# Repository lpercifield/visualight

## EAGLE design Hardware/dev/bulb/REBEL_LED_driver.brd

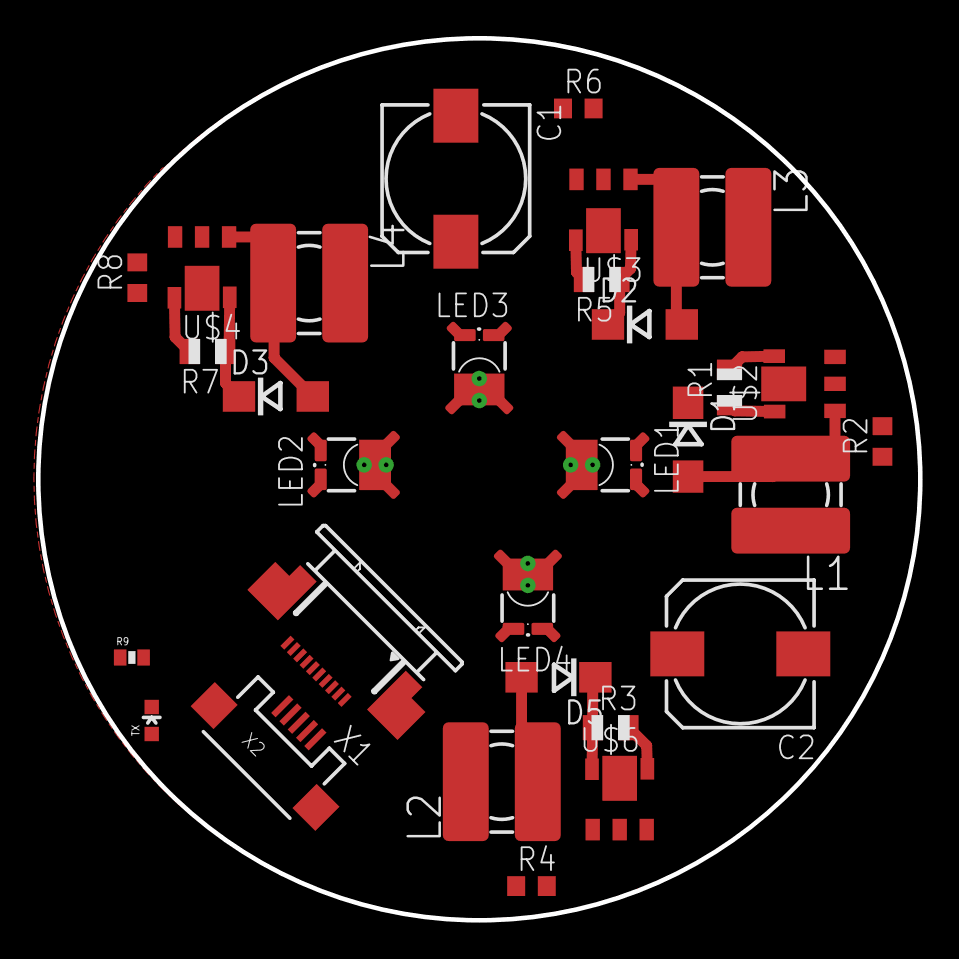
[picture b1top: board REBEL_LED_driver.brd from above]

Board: 2 copper layers, 49.0 x 49.0 mm, 30 parts (0 on the bottom side), 28 nets.

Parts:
C1, C2: 150uF; 175TMP-0810
D1, D2, D3, D5: SCHOTTKY; DO214AC
L1, L2, L3, L4: 47uH; TDK6045
LED1, LED2, LED3, LED4: LUXEON_REBEL
R1, R3, R5, R7: 0.14; R0805
R2, R4, R6, R8: 10K; R0603
R9: 330; 0402-RES
TX: Green; LED-0603
U$2, U$3, U$4, U$6: ZLED7000-LEDDRIVER; SOT89-5
X1: 52745-1090
X2: USB-MICROB

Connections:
D5: R6.1, X1.3
D9: R2.1, X1.5
D10: R8.1, X1.4
D13: R4.1, X1.2
D+IN: X1.7, X2.D+
D-IN: X1.8, X2.D-
GND: C1.-, C2.-, U$2.2, U$3.2, U$4.2, U$6.2, X1.9, X2.GND
unnamed: R2.2, U$2.3
unnamed: R9.2, TX.C
unnamed: LED1.A, LED1.A@1, R1.2, U$2.4
unnamed: L1.1, LED1.C, LED1.C@1
unnamed: D1.A, L1.2, U$2.1
unnamed: LED4.A, LED4.A@1, R3.2, U$6.4
unnamed: D5.A, L2.2, U$6.1
unnamed: R4.2, U$6.3
unnamed: LED3.A, LED3.A@1, R5.2, U$3.4
unnamed: D2.A, L3.2, U$3.1
unnamed: R6.2, U$3.3
unnamed: LED2.A, LED2.A@1, R7.2, U$4.4
unnamed: D3.A, L4.2, U$4.1
unnamed: R8.2, U$4.3
unnamed: L4.1, LED2.C, LED2.C@1
unnamed: L2.1, LED4.C, LED4.C@1
unnamed: L3.1, LED3.C, LED3.C@1
TH: LED1.TH, LED1.TH@1, LED1.TH@2, LED1.TH@3, LED1.TH@4, LED2.TH, LED2.TH@1, LED2.TH@2, LED2.TH@3, LED2.TH@4, LED3.TH, LED3.TH@1, LED3.TH@2, LED3.TH@3, LED3.TH@4, LED4.TH, LED4.TH@1, LED4.TH@2, LED4.TH@3, LED4.TH@4
TXLED: R9.1, X1.6
UVCC: TX.A, X1.1, X2.VBUS
VCC: C1.+, C2.+, D1.C, D2.C, D3.C, D5.C, R1.1, R3.1, R5.1, R7.1, U$2.5, U$3.5, U$4.5, U$6.5, X1.10

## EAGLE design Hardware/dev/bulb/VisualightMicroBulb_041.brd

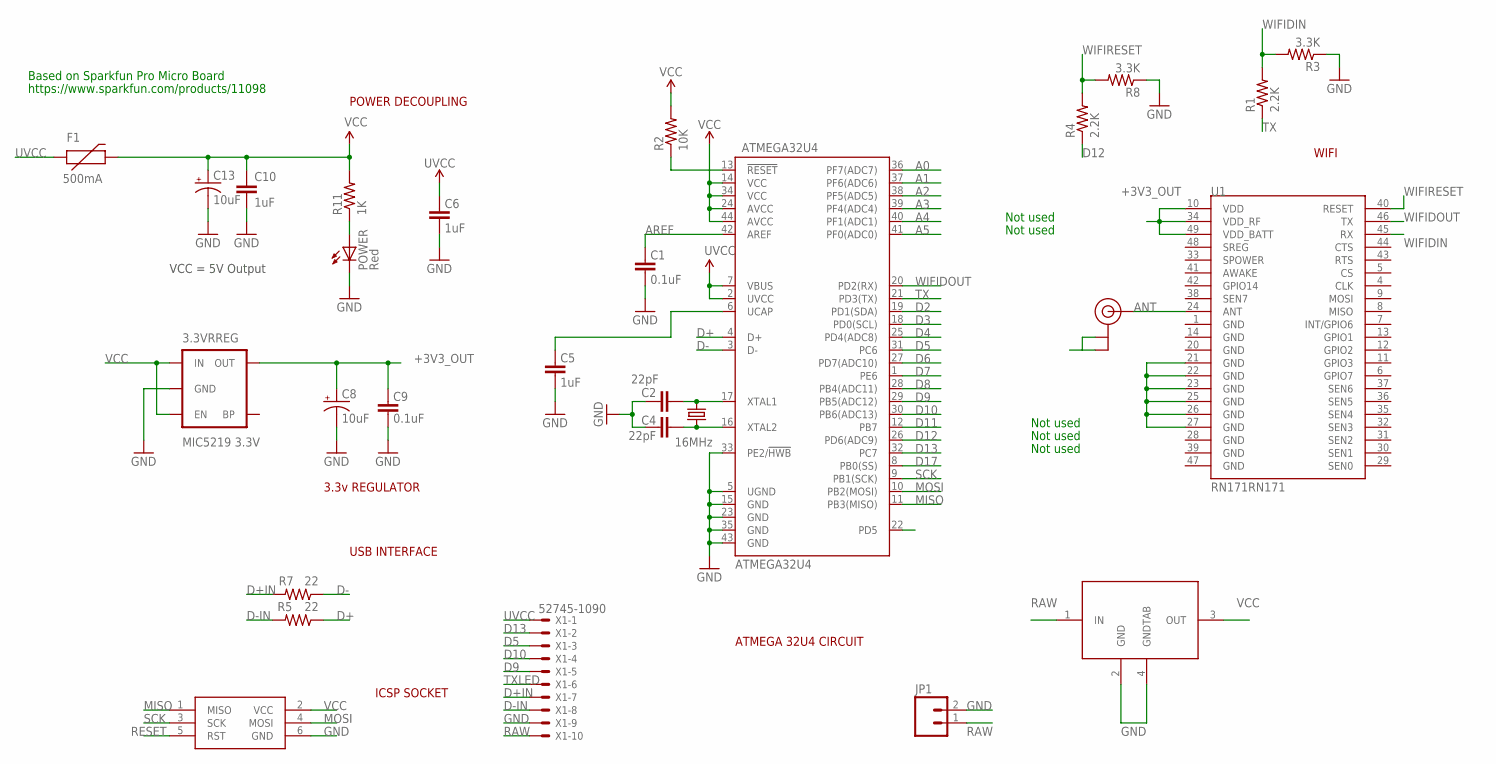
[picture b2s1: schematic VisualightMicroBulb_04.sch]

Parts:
3.3VRREG: MIC5219 3.3V; SOT23-5
ATMEGA32U4: ATMEGA32U4; SPARKFUN-DIGITALIC_TQFP44
C1, C9: 0.1uF; 0402-CAP
C2, C4: 22pF; 0402-CAP
C5, C6, C10: 1uF; 0402-CAP
C8, C13: 10uF; EIA3216
F1: 500mA; PTC-1206
ISP1: AVRISP-6; AVRISP
JP1: M02PTH; 1X02
POWER: Red; LED-0603
R1, R4: 2.2K; 0402-RES
R2: 10K; 0402-RES
R3, R8: 3.3K; 0402-RES
R5, R7: 22; 0402-RES
R11: 1K; 0402-RES
U1: RN171RN171; RN171
U$1: U.FL
U$2: MIC5239; SOT223
X1: 52745-1090
Y1: 16MHz; CRYSTAL-SMD-5X3

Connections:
+3V3_OUT: 3.3VRREG.5 (OUT), C8.A (+), C9.2, U1.10 (VDD), U1.34 (VDD_RF), U1.49 (VDD_BATT)
A0: ATMEGA32U4.36 (PF7(ADC7))
A1: ATMEGA32U4.37 (PF6(ADC6))
A2: ATMEGA32U4.38 (PF5(ADC5))
A3: ATMEGA32U4.39 (PF4(ADC4))
A4: ATMEGA32U4.40 (PF1(ADC1))
A5: ATMEGA32U4.41 (PF0(ADC0))
ANT: U1.24 (ANT), U$1.P$3 (SIGNAL)
AREF: ATMEGA32U4.42 (AREF), C1.2
D2: ATMEGA32U4.19 (PD1(SDA))
D3: ATMEGA32U4.18 (PD0(SCL))
D4: ATMEGA32U4.25 (PD4(ADC8))
D5: ATMEGA32U4.31 (PC6), X1.3
D6: ATMEGA32U4.27 (PD7(ADC10))
D7: ATMEGA32U4.1 (PE6)
D8: ATMEGA32U4.28 (PB4(ADC11))
D9: ATMEGA32U4.29 (PB5(ADC12)), X1.5
D10: ATMEGA32U4.30 (PB6(ADC13)), X1.4
D11: ATMEGA32U4.12 (PB7)
D12: ATMEGA32U4.26 (PD6(ADC9)), R4.1
D13: ATMEGA32U4.32 (PC7), X1.2
D17: ATMEGA32U4.8 (PB0(SS))
D+: ATMEGA32U4.4 (D+), R5.1
D+IN: R7.2, X1.7
D-: ATMEGA32U4.3 (D-), R7.1
D-IN: R5.2, X1.8
GND: 3.3VRREG.2 (GND), ATMEGA32U4.5 (UGND), ATMEGA32U4.15 (GND), ATMEGA32U4.23 (GND), ATMEGA32U4.33 (PE2/!HWB), ATMEGA32U4.35 (GND), ATMEGA32U4.43 (GND), C1.1, C2.2, C4.2, C5.1, C6.1, C8.C (-), C9.1, C10.2, C13.C (-), ISP1.6 (GND), JP1.2, POWER.C, R3.1, R8.1, U1.21 (GND), U1.22 (GND), U1.23 (GND), U1.25 (GND), U1.26 (GND), U1.27 (GND), U$1.P$1 (GND), U$1.P$2 (GND), U$2.2 (GND), U$2.4 (GNDTAB), X1.9
MISO: ATMEGA32U4.11 (PB3(MISO)), ISP1.1 (MISO)
MOSI: ATMEGA32U4.10 (PB2(MOSI)), ISP1.4 (MOSI)
unnamed: ATMEGA32U4.16 (XTAL2), C4.1, Y1.1
unnamed: ATMEGA32U4.17 (XTAL1), C2.1, Y1.3 (2)
unnamed: ATMEGA32U4.6 (UCAP), C5.2
unnamed: POWER.A, R11.1
RAW: JP1.1, U$2.1 (IN), X1.10
RESET: ATMEGA32U4.13 (!RESET), ISP1.5 (RST), R2.1
SCK: ATMEGA32U4.9 (PB1(SCK)), ISP1.3 (SCK)
TX: ATMEGA32U4.21 (PD3(TX)), R1.1
TXLED: ATMEGA32U4.22 (PD5), X1.6
UVCC: ATMEGA32U4.2 (UVCC), ATMEGA32U4.7 (VBUS), C6.2, F1.1, X1.1
VCC: 3.3VRREG.1 (IN), 3.3VRREG.3 (EN), ATMEGA32U4.14 (VCC), ATMEGA32U4.24 (AVCC), ATMEGA32U4.34 (VCC), ATMEGA32U4.44 (AVCC), C10.1, C13.A (+), F1.2, ISP1.2 (VCC), R2.2, R11.2, U$2.3 (OUT)
WIFIDIN: R1.2, R3.2, U1.45 (RX)
WIFIDOUT: ATMEGA32U4.20 (PD2(RX)), U1.46 (TX)
WIFIRESET: R4.2, R8.2, U1.40 (RESET)

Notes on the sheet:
VCC = 5V Output
Not used
Based on Sparkfun Pro Micro Board
https://www.sparkfun.com/products/11098
USB INTERFACE
ICSP SOCKET
3.3v REGULATOR
POWER DECOUPLING
ATMEGA 32U4 CIRCUIT
WIFI

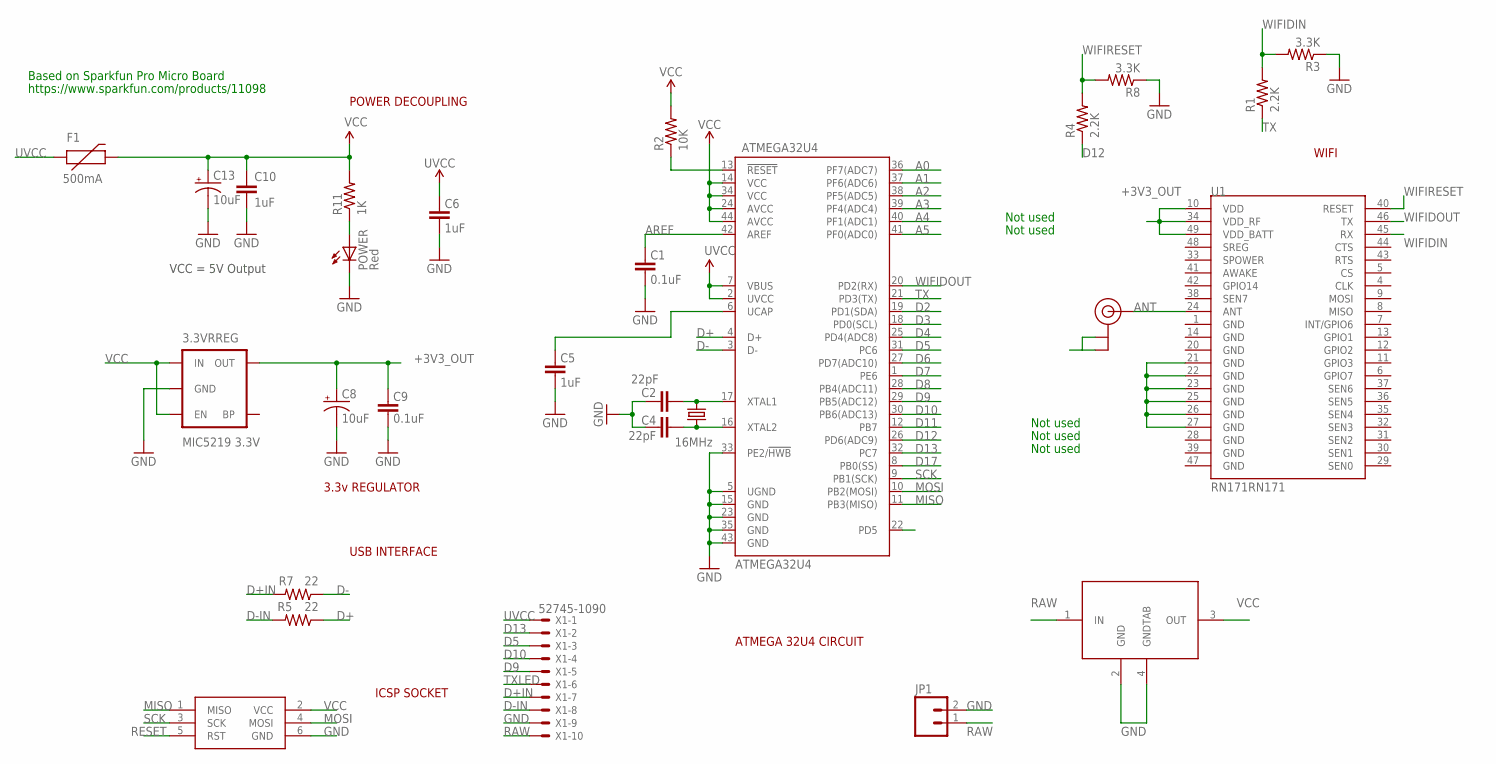
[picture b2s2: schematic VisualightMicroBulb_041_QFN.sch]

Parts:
3.3VRREG: MIC5219 3.3V; SOT23-5
ATMEGA32U4: ATMEGA32U4; SPARKFUN-DIGITALIC_TQFP44
C1, C9: 0.1uF; 0402-CAP
C2, C4: 22pF; 0402-CAP
C5, C6, C10: 1uF; 0402-CAP
C8, C13: 10uF; EIA3216
F1: 500mA; PTC-1206
ISP1: AVRISP-6; AVRISP
JP1: M02PTH; 1X02
POWER: Red; LED-0603
R1, R4: 2.2K; 0402-RES
R2: 10K; 0402-RES
R3, R8: 3.3K; 0402-RES
R5, R7: 22; 0402-RES
R11: 1K; 0402-RES
U1: RN171RN171; RN171
U$1: U.FL
U$2: MIC5239; SOT223
X1: 52745-1090
Y1: 16MHz; CRYSTAL-SMD-5X3

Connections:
+3V3_OUT: 3.3VRREG.5 (OUT), C8.A (+), C9.2, U1.10 (VDD), U1.34 (VDD_RF), U1.49 (VDD_BATT)
A0: ATMEGA32U4.36 (PF7(ADC7))
A1: ATMEGA32U4.37 (PF6(ADC6))
A2: ATMEGA32U4.38 (PF5(ADC5))
A3: ATMEGA32U4.39 (PF4(ADC4))
A4: ATMEGA32U4.40 (PF1(ADC1))
A5: ATMEGA32U4.41 (PF0(ADC0))
ANT: U1.24 (ANT), U$1.P$3 (SIGNAL)
AREF: ATMEGA32U4.42 (AREF), C1.2
D2: ATMEGA32U4.19 (PD1(SDA))
D3: ATMEGA32U4.18 (PD0(SCL))
D4: ATMEGA32U4.25 (PD4(ADC8))
D5: ATMEGA32U4.31 (PC6), X1.3
D6: ATMEGA32U4.27 (PD7(ADC10))
D7: ATMEGA32U4.1 (PE6)
D8: ATMEGA32U4.28 (PB4(ADC11))
D9: ATMEGA32U4.29 (PB5(ADC12)), X1.5
D10: ATMEGA32U4.30 (PB6(ADC13)), X1.4
D11: ATMEGA32U4.12 (PB7)
D12: ATMEGA32U4.26 (PD6(ADC9)), R4.1
D13: ATMEGA32U4.32 (PC7), X1.2
D17: ATMEGA32U4.8 (PB0(SS))
D+: ATMEGA32U4.4 (D+), R5.1
D+IN: R7.2, X1.7
D-: ATMEGA32U4.3 (D-), R7.1
D-IN: R5.2, X1.8
GND: 3.3VRREG.2 (GND), ATMEGA32U4.5 (UGND), ATMEGA32U4.15 (GND), ATMEGA32U4.23 (GND), ATMEGA32U4.33 (PE2/!HWB), ATMEGA32U4.35 (GND), ATMEGA32U4.43 (GND), C1.1, C2.2, C4.2, C5.1, C6.1, C8.C (-), C9.1, C10.2, C13.C (-), ISP1.6 (GND), JP1.2, POWER.C, R3.1, R8.1, U1.21 (GND), U1.22 (GND), U1.23 (GND), U1.25 (GND), U1.26 (GND), U1.27 (GND), U$1.P$1 (GND), U$1.P$2 (GND), U$2.2 (GND), U$2.4 (GNDTAB), X1.9
MISO: ATMEGA32U4.11 (PB3(MISO)), ISP1.1 (MISO)
MOSI: ATMEGA32U4.10 (PB2(MOSI)), ISP1.4 (MOSI)
unnamed: ATMEGA32U4.16 (XTAL2), C4.1, Y1.1
unnamed: ATMEGA32U4.17 (XTAL1), C2.1, Y1.3 (2)
unnamed: ATMEGA32U4.6 (UCAP), C5.2
unnamed: POWER.A, R11.1
RAW: JP1.1, U$2.1 (IN), X1.10
RESET: ATMEGA32U4.13 (!RESET), ISP1.5 (RST), R2.1
SCK: ATMEGA32U4.9 (PB1(SCK)), ISP1.3 (SCK)
TX: ATMEGA32U4.21 (PD3(TX)), R1.1
TXLED: ATMEGA32U4.22 (PD5), X1.6
UVCC: ATMEGA32U4.2 (UVCC), ATMEGA32U4.7 (VBUS), C6.2, F1.1, X1.1
VCC: 3.3VRREG.1 (IN), 3.3VRREG.3 (EN), ATMEGA32U4.14 (VCC), ATMEGA32U4.24 (AVCC), ATMEGA32U4.34 (VCC), ATMEGA32U4.44 (AVCC), C10.1, C13.A (+), F1.2, ISP1.2 (VCC), R2.2, R11.2, U$2.3 (OUT)
WIFIDIN: R1.2, R3.2, U1.45 (RX)
WIFIDOUT: ATMEGA32U4.20 (PD2(RX)), U1.46 (TX)
WIFIRESET: R4.2, R8.2, U1.40 (RESET)

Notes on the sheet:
VCC = 5V Output
Not used
Based on Sparkfun Pro Micro Board
https://www.sparkfun.com/products/11098
USB INTERFACE
ICSP SOCKET
3.3v REGULATOR
POWER DECOUPLING
ATMEGA 32U4 CIRCUIT
WIFI

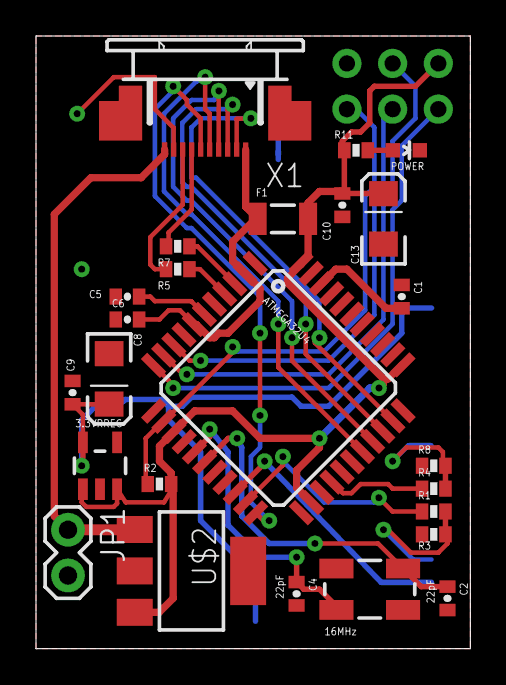
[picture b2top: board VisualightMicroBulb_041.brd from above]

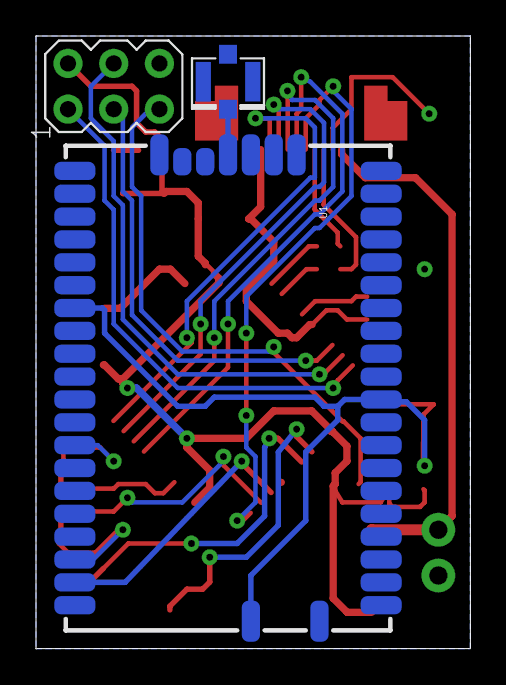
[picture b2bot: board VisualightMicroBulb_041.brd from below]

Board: 2 copper layers, 24.1 x 34.0 mm, 28 parts (3 on the bottom side), 29 nets.

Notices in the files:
parts and their libraries:
SparkFun-Connectors: Licensing: CC v3.0 Share-Alike You are welcome to use this library for commercial purposes.
